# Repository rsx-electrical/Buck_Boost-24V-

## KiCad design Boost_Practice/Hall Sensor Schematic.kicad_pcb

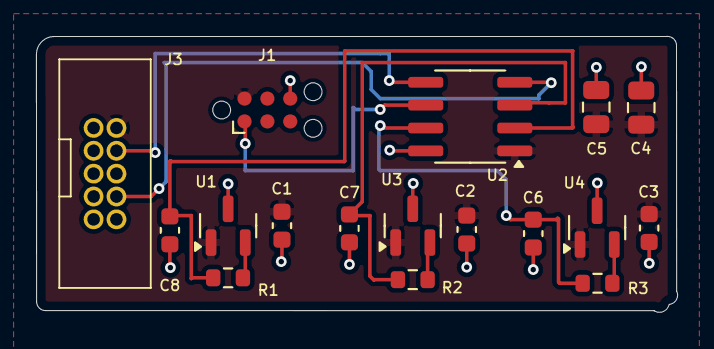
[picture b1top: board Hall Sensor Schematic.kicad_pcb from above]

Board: 2 copper layers, 35.6 x 15.3 mm, 17 parts (0 on the bottom side), 11 nets.

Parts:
C1, C2, C3, C6, C7, C8: 0.1u; C_0603_1608Metric
C4: 0u1; C_0805_2012Metric
C5: 1u; C_0805_2012Metric
J1: TC2030-IDC-NL; Tag-Connect_TC2030-IDC-FP_2x03_P1.27mm_Vertical
J3: Conn_02x05_Odd_Even; Half_Pitch_IDC_2x5
R1, R2, R3: 100R; R_0603_1608Metric
U1, U3, U4: DRV5055A3xDBZxQ1; SOT-23
U2: ATtiny202-SS; SOIC-8_3.9x4.9mm_P1.27mm

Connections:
+5V: C1.1, C2.1, C3.1, C4.1, C5.1, J1.2 (VDD), J3.2, U1.1 (VCC), U2.1 (VCC), U3.1 (VCC), U4.1 (VCC)
/F_lim_dig: J3.4, U2.5 (PA2)
/Hall_1: C8.1, R1.1, U2.2 (PA6)
/Hall_2: C7.1, R2.1, U2.3 (PA7)
/Hall_3: C6.1, R3.1, U2.7 (PA3)
/Out_1: R1.2, U1.2 (OUT)
/Out_2: R2.2, U3.2 (OUT)
/Out_3: R3.2, U4.2 (OUT)
/Program: J1.1 (DATA), U2.6 (~RESET/PA0)
/R_lim_dig: J3.8, U2.4 (PA1)
GND: C1.2, C2.2, C3.2, C4.2, C5.2, C6.2, C7.2, C8.2, J1.6 (GND), J3.10, U1.3 (GND), U2.8 (GND), U3.3 (GND), U4.3 (GND)

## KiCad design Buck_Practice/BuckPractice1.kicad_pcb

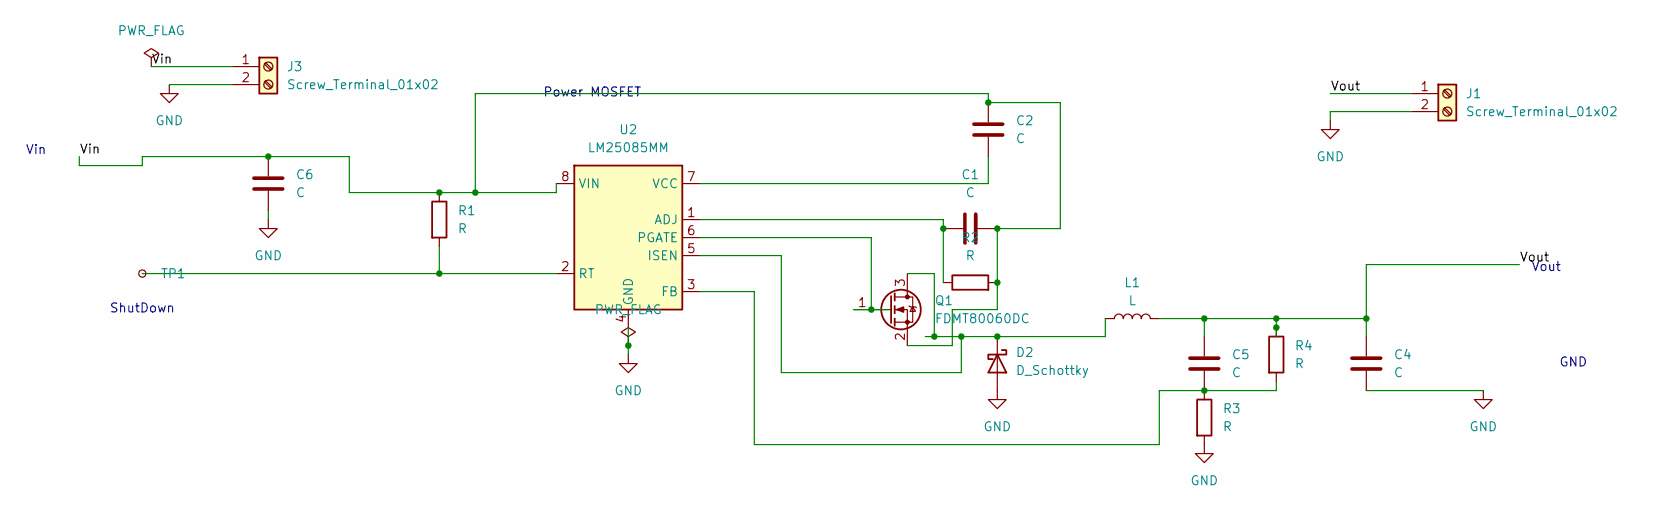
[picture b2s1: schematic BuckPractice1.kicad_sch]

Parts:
C1, C5: C; C_0805_2012Metric; MPN CL21B105KBFNNNE
C2, C4, C6: C; C_Elec_10x10.2
D2: D_Schottky; D_SMA
J1, J3: Screw_Terminal_01x02; TerminalBlock_4Ucon_1x02_P3.50mm_Vertical
L1: L; L_Coilcraft_XAL1350-XXX
Q1: FDMT80060DC; PQFN_8x8
R1, R2, R3, R4: R; R_0805_2012Metric
TP1: TestPoint_Small; TestPoint_Pad_D1.0mm
U2: LM25085MM; MSOP-8_3x3mm_P0.65mm

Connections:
/Vin: C1.2, C2.1, C6.1, J3.1, Q1.2 (S), R1.1, R2.2, U2.8 (VIN)
/Vout: C4.1, C5.2, J1.1, L1.2, R4.1
GND: C4.2, C6.2, D2.2 (A), J1.2, J3.2, R3.2, U2.4 (GND)
unnamed: D2.1 (K), L1.1, Q1.3 (D), U2.5 (ISEN)
unnamed: Q1.1 (G), U2.6 (PGATE)
unnamed: C1.1, R2.1, U2.1 (ADJ)
unnamed: C5.1, R3.1, R4.2, U2.3 (FB)
unnamed: R1.2, TP1.1, U2.2 (RT)
unnamed: C2.2, U2.7 (VCC)

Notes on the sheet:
GND
Vin
Vout
Power MOSFET
ShutDown

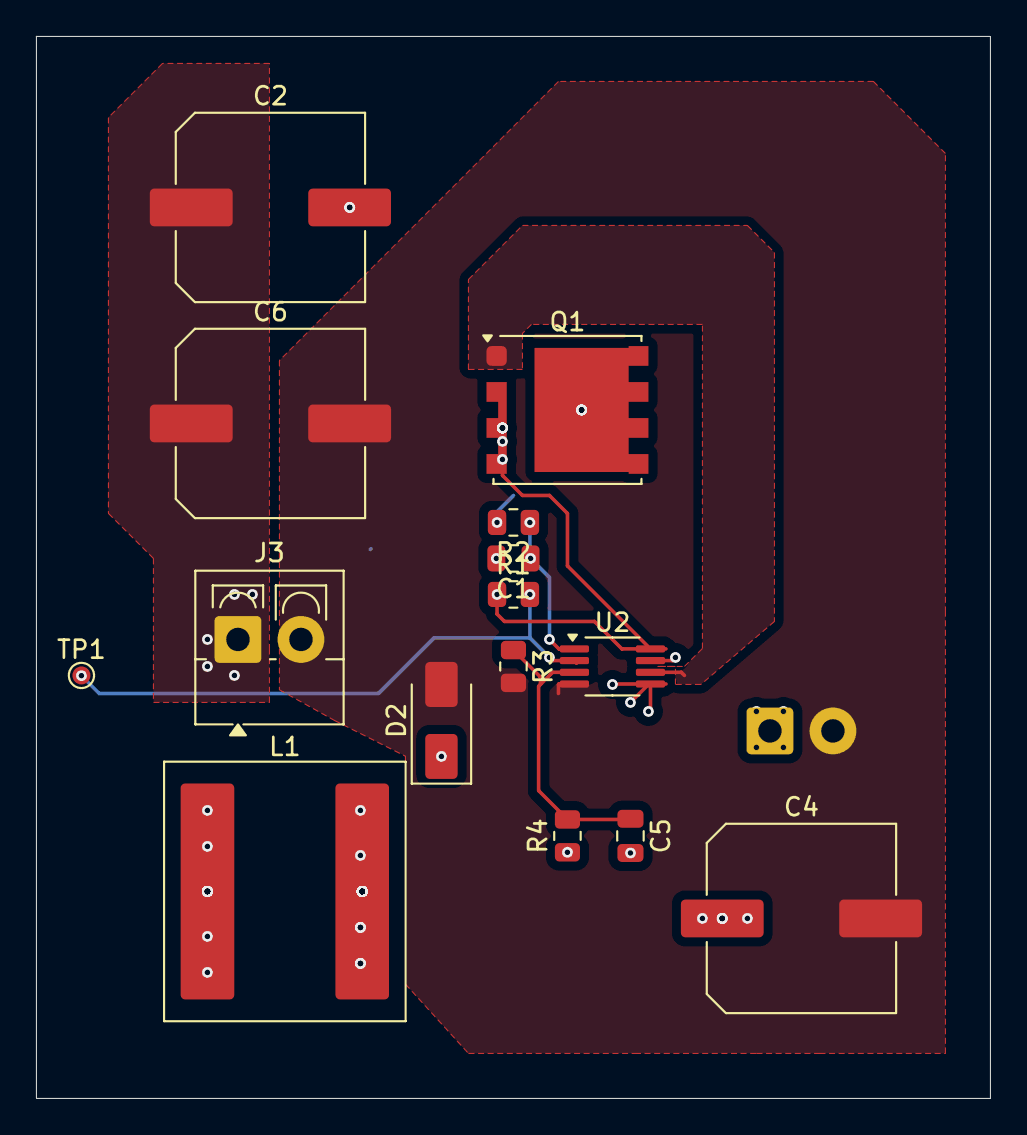
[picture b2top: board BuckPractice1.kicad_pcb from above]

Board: 2 copper layers, 53.0 x 59.0 mm, 16 parts (1 on the bottom side), 9 nets.
